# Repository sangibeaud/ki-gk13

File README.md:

Various kica files and projects for the GK13 guitar eco-system

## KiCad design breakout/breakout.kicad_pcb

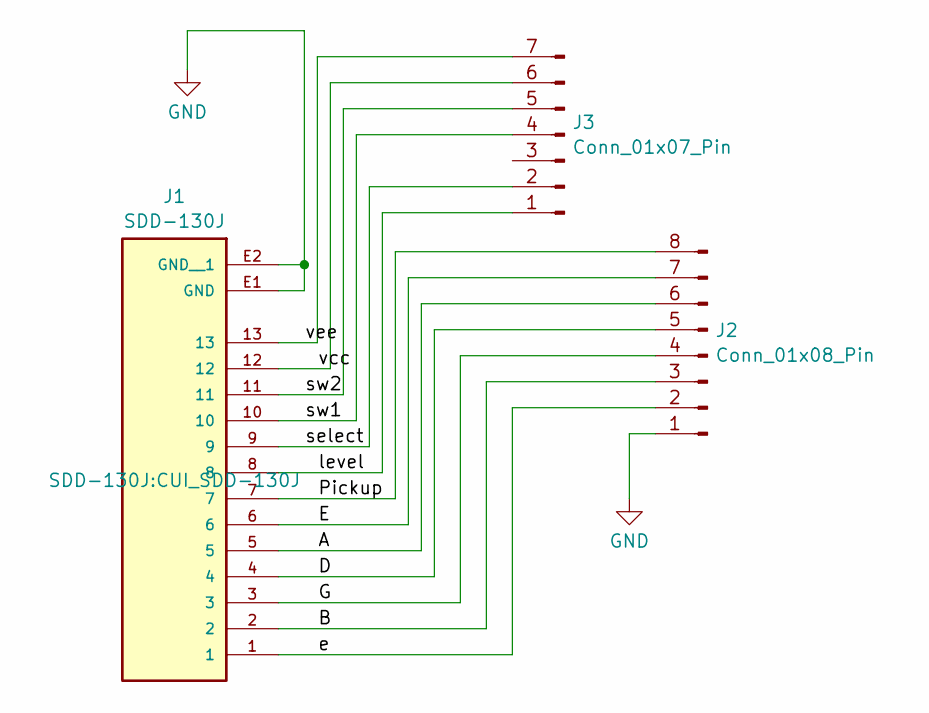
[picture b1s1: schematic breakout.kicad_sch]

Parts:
J1: SDD-130J; CUI_SDD-130J; PARTREV 1.06/02-13-2020
J2: Conn_01x08_Pin; PinHeader_1x08_P2.54mm_Vertical
J3: Conn_01x07_Pin; PinHeader_1x07_P2.54mm_Vertical

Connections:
/A: J1.5, J2.6
/B: J1.2, J2.3
/D: J1.4, J2.5
/E: J1.6, J2.7
/G: J1.3, J2.4
/Pickup: J1.7, J2.8
/e: J1.1, J2.2
/level: J1.8, J3.1
/select: J1.9, J3.2
/sw1: J1.10, J3.4
/sw2: J1.11, J3.5
/vcc: J1.12, J3.6
/vee: J1.13, J3.7
GND: J1.E1 (GND), J1.E2 (GND__1), J2.1

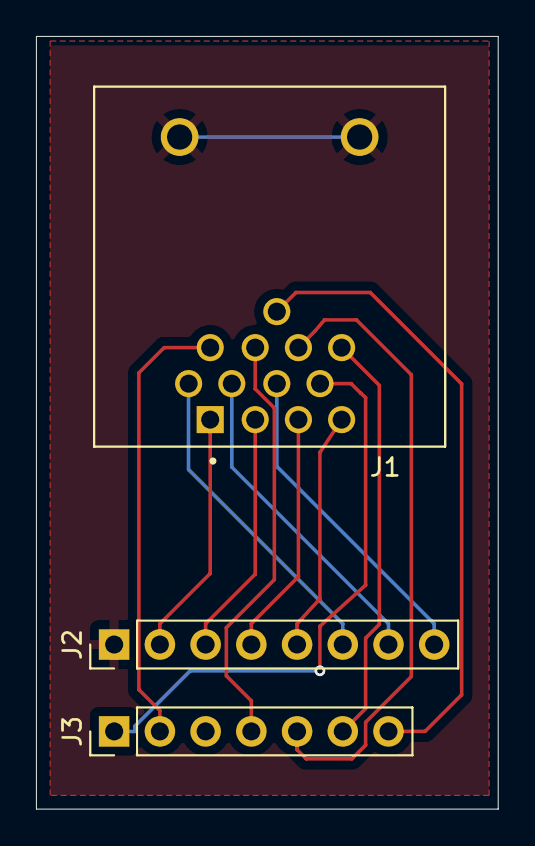
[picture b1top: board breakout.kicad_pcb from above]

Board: 2 copper layers, 25.7 x 42.9 mm, 3 parts (0 on the bottom side), 14 nets.

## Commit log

2025-02-06 Add breakout
2025-02-06 Add doc
2025-02-06 File rename
2025-02-06 global setup image for kit version
